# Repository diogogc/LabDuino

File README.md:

# LabDuino
###EN
This project is my contribution STEM driven classes, in order to help teachers and students on science learning. It's an Arduino based project, feel free to fork or contribute to make it better, or just download, build it yourself or on your classes.

Main Components:

- 1 x Arduino Pro Mini 328 5V;

- 2 x PCF8574P Port expander;

- 1x 16x2 Display;

Voltage Regulator:

I actually followed this instructables for that: <http://www.instructables.com/id/Portable-5V-Regulator/>

I just changed the 78L05 with L7805CV, because i already had a few of them around.

Other

- 8 x 10k Ohms resistor

- 4 x 330 Ohms resistor

- 10k Ohms trimpot

- 2 x 16 pins IC socket (for PCF8574P);

- 16 vias flat 28AWG cable

- 8 x headphone jack (we gonna use it to connect sensors)

For more information, please check the Wiki page.

If you want to become a collaborator, please fill this form:
http://goo.gl/dhk8Ny

###PT-br
Este Projeto é minha contribição para aulas voltadas a STEM, para ajudar professores e alunos no aprendizado de ciências. É um projeto baseado em arduino. Sinta-se livre para fazer fork ou contribuir para fazer este projeto melhor, ou apenas baixe e construa e utilize em suas turmas.

Componentes Principais:

- 1 x Arduino Pro Mini 328 5V;

- 2 x PCF8574P Port expander;

- 1x 16x2 Display;

Regulador de Voltagem:

Eu segui as seguintes instruções: <http://www.instructables.com/id/Portable-5V-Regulator/>

Eu mudei o 78L05 pelo L7805CV porque já tinha alguns aqui comigo.

Outros

- 8 x 10k Ohms resistor

- 4 x 330 Ohms resistor

- 10k Ohms trimpot

- 2 x 16 pinos CI socket (para o PCF8574P);

- Cabo de 16 vias flat 28AWG

- 8 x headphone jack (Usado para conectar os sensores)

Para mais informações, porfavor consulte a pagina Wiki.

Se você quiser se tornar um colaborador, porfavor preencha este formulário:
http://goo.gl/dhk8Ny

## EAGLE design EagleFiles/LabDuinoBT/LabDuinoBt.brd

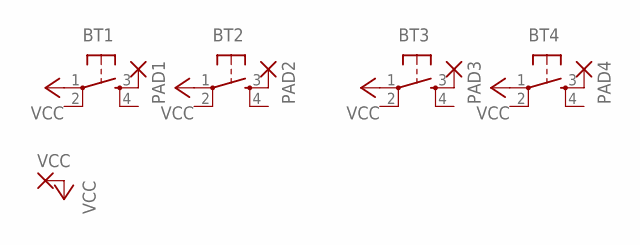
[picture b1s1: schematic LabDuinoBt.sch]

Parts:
BT1, BT2, BT3, BT4: TAC_SWITCHPTH; TACTILE-PTH
PAD1, PAD2, PAD3, PAD4: 1,6/0,9
VCC: 1,6/0,9

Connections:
unnamed: BT1.3, PAD1.1
unnamed: BT2.3, PAD2.1
unnamed: BT3.3, PAD3.1
unnamed: BT4.3, PAD4.1
VCC: BT1.1, BT2.1, BT3.1, BT4.1, VCC.1

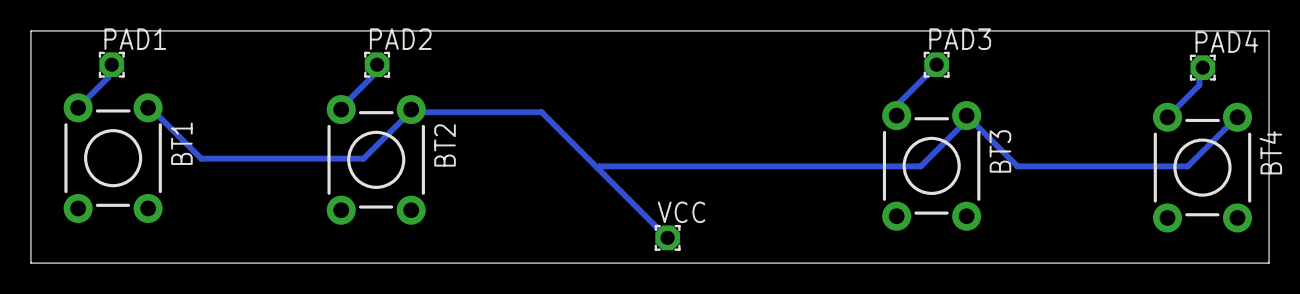
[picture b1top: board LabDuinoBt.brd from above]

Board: 2 copper layers, 80.0 x 15.0 mm, 9 parts (0 on the bottom side), 5 nets.

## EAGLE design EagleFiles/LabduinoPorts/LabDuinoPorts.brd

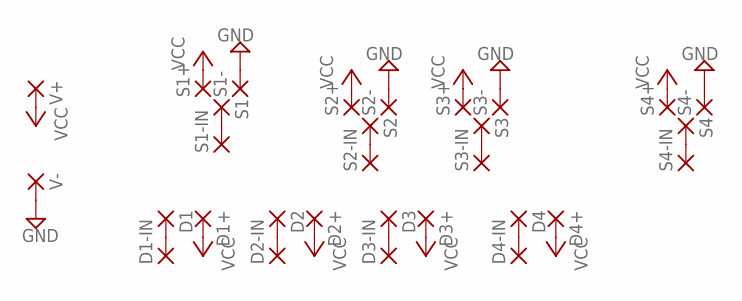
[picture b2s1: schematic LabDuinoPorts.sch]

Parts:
D1, D1+, D1-IN, D2, D2+, D2-IN, D3, D3+, D3-IN, D4, D4+, D4-IN: 2,54/0,9
S1, S1+, S1-, S1-IN, S2, S2+, S2-, S2-IN, S3, S3+, S3-, S3-IN, S4, S4+, S4-, S4-IN: 2,54/0,9
V+: 2,54/0,9
V-: 2,54/0,9

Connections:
GND: S1-.1, S2-.1, S3-.1, S4-.1, V-.1
unnamed: S1.1, S1-IN.1
unnamed: S2.1, S2-IN.1
unnamed: S3.1, S3-IN.1
unnamed: S4.1, S4-IN.1
unnamed: D1.1, D1-IN.1
unnamed: D2.1, D2-IN.1
unnamed: D3.1, D3-IN.1
unnamed: D4.1, D4-IN.1
VCC: D1+.1, D2+.1, D3+.1, D4+.1, S1+.1, S2+.1, S3+.1, S4+.1, V+.1

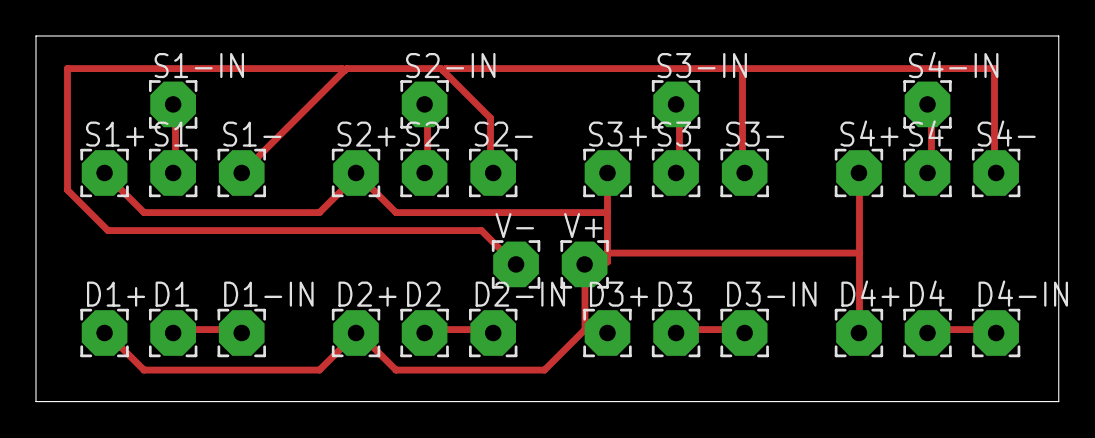
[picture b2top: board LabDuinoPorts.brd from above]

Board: 2 copper layers, 56.8 x 20.3 mm, 30 parts (0 on the bottom side), 10 nets.

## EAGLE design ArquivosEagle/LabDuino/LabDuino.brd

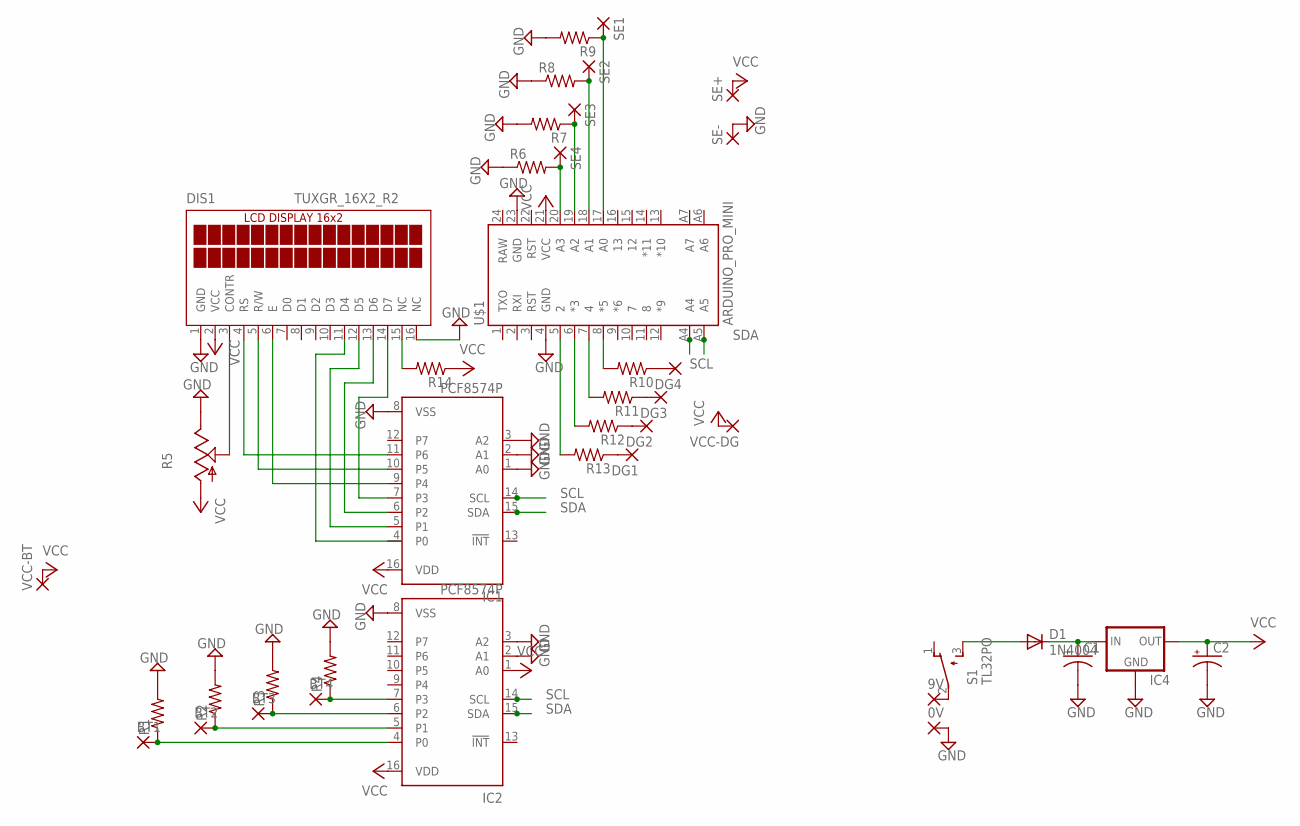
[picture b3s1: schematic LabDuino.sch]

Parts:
0V, 9V: 2,54/1,1
BT1, BT2, BT3, BT4: 1,6/0,9
C1, C2: CPOL-USE2-4; E2-4
D1: 1N4004; DO41-10
DG1, DG2, DG3, DG4: 1,6/0,9
DIS1: TUXGR_16X2_R2
IC1, IC2: PCF8574P; DIL16
IC4: V_REG_78XX-TO-220; TO-220-ALT
R1, R2, R3, R4, R10, R11, R12, R13, R14: RESISTORPTH-1/6W; 1/6W-RES
R5: TRIM_US-RS3; RS3
R6, R7, R8, R9: R-US_0204/7; 0204/7
S1: TL32PO; TL3XPO
SE1, SE2, SE3, SE4: 1,6/0,9
SE+: 1,6/0,9
SE-: 1,6/0,9
U$1: ARDUINO_PRO_MINI
VCC-BT: 1,6/0,9
VCC-DG: 1,6/0,9

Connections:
10K: BT2.1, IC2.5 (P1), R2.1
GND: 0V.1, C1.-, C2.-, DIS1.1 (GND), DIS1.16 (NC), IC1.1 (A0), IC1.2 (A1), IC1.3 (A2), IC1.8 (VSS), IC2.2 (A1), IC2.3 (A2), IC2.8 (VSS), IC4.GND, R1.2, R2.2, R3.2, R4.2, R5.E, R6.1, R7.2, R8.1, R9.2, SE-.1, U$1.4 (GND), U$1.23 (GND)
unnamed: R6.2, SE4.1, U$1.20 (A3)
unnamed: BT1.1, IC2.4 (P0), R1.1
unnamed: 9V.1, S1.2
unnamed: BT3.1, IC2.6 (P2), R3.1
unnamed: BT4.1, IC2.7 (P3), R4.1
unnamed: R7.1, SE3.1, U$1.19 (A2)
unnamed: DIS1.4 (RS), IC1.11 (P6)
unnamed: DIS1.5 (R/W), IC1.10 (P5)
unnamed: DIS1.6 (E), IC1.9 (P4)
unnamed: DIS1.14 (D7), IC1.7 (P3)
unnamed: DIS1.13 (D6), IC1.6 (P2)
unnamed: DIS1.12 (D5), IC1.5 (P1)
unnamed: DIS1.3 (CONTR), R5.S
unnamed: D1.A, S1.3 (S)
unnamed: C1.+, D1.C, IC4.IN
unnamed: R8.2, SE2.1, U$1.18 (A1)
unnamed: R9.1, SE1.1, U$1.17 (A0)
unnamed: R13.2, U$1.5 (2)
unnamed: R12.2, U$1.6 (*3)
unnamed: R11.2, U$1.7 (4)
unnamed: R10.2, U$1.8 (*5)
unnamed: DG1.1, R13.1
unnamed: DG2.1, R12.1
unnamed: DG3.1, R11.1
unnamed: DG4.1, R10.1
unnamed: DIS1.15 (NC), R14.2
SCL: IC1.14 (SCL), IC2.14 (SCL), U$1.A4
SDA: IC1.15 (SDA), IC2.15 (SDA), U$1.A5
VCC: C2.+, DIS1.2 (VCC), IC1.16 (VDD), IC2.1 (A0), IC2.16 (VDD), IC4.OUT, R5.A, R14.1, SE+.1, U$1.21 (VCC), VCC-BT.1, VCC-DG.1

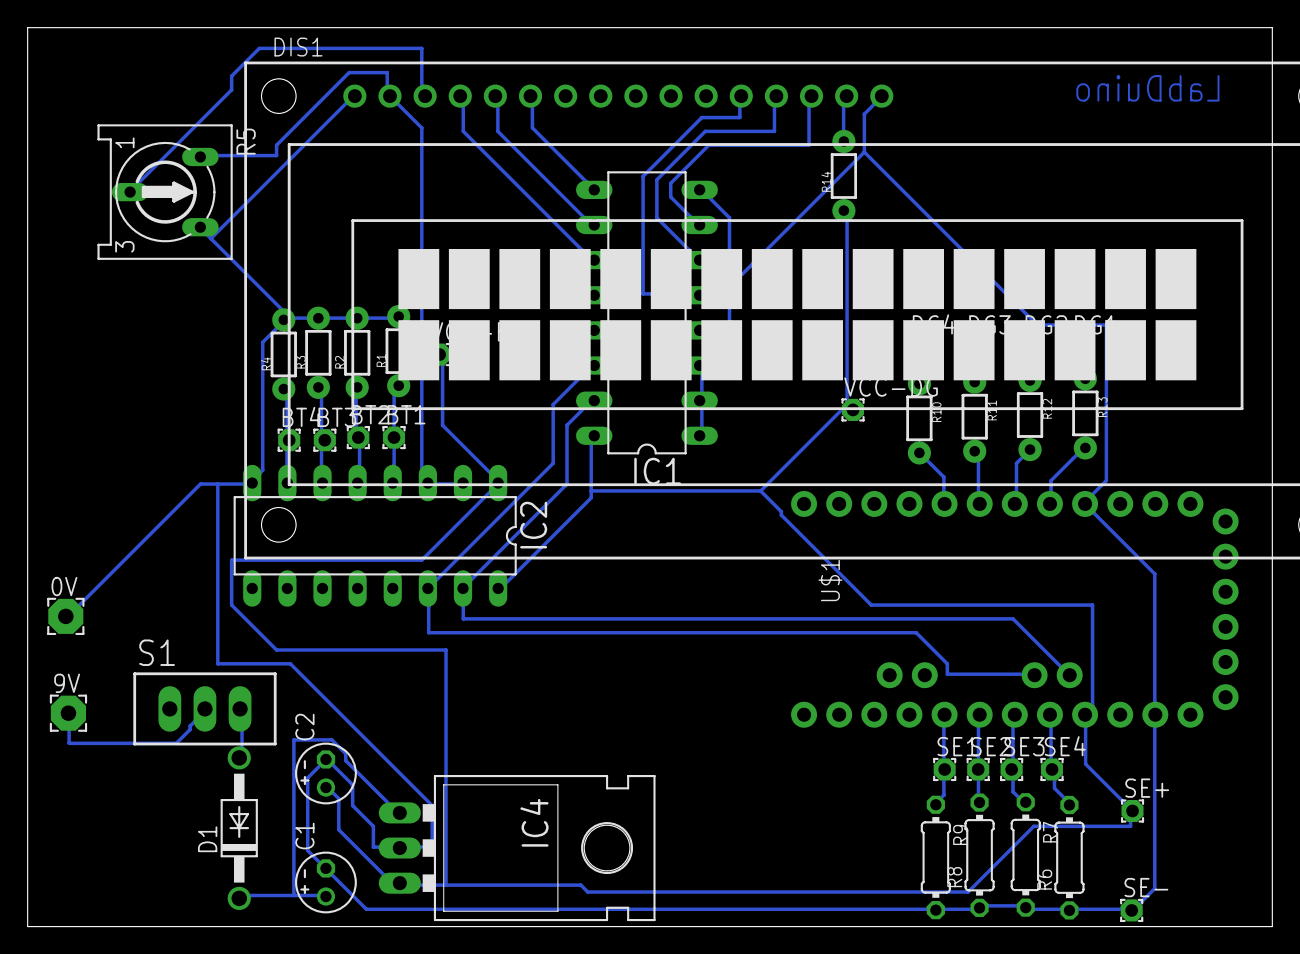
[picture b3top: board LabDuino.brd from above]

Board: 2 copper layers, 90.0 x 65.0 mm, 41 parts (0 on the bottom side), 31 nets.

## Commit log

2015-02-11 Arquivos Eagle e Codigo
2015-02-12 Added Comments
2015-02-12 License
2015-02-12 More Comments
2015-02-12 Experimento Velocidade Média
2015-02-12 Velocidade Instantanea
2015-02-20 Board Update
2015-02-20 Better folder names
2015-02-20 Update README.md
    Added Portuguese translation
2015-02-20 Sensor Ports / Button board adjustment
2015-02-20 Laser Cutter Files
2015-02-20 Name correction
2015-02-21 Eagle LabDuinoPorts Update
2015-02-21 LabDuino Box Update
2015-02-22 Button Board UpDate
2015-09-20 FreeFall

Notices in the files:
parts and their libraries:
SparkFun-PowerIC: Licensing: Creative Commons ShareAlike 4.0 International - https://creativecommons.org/licenses/by-sa/4.0
